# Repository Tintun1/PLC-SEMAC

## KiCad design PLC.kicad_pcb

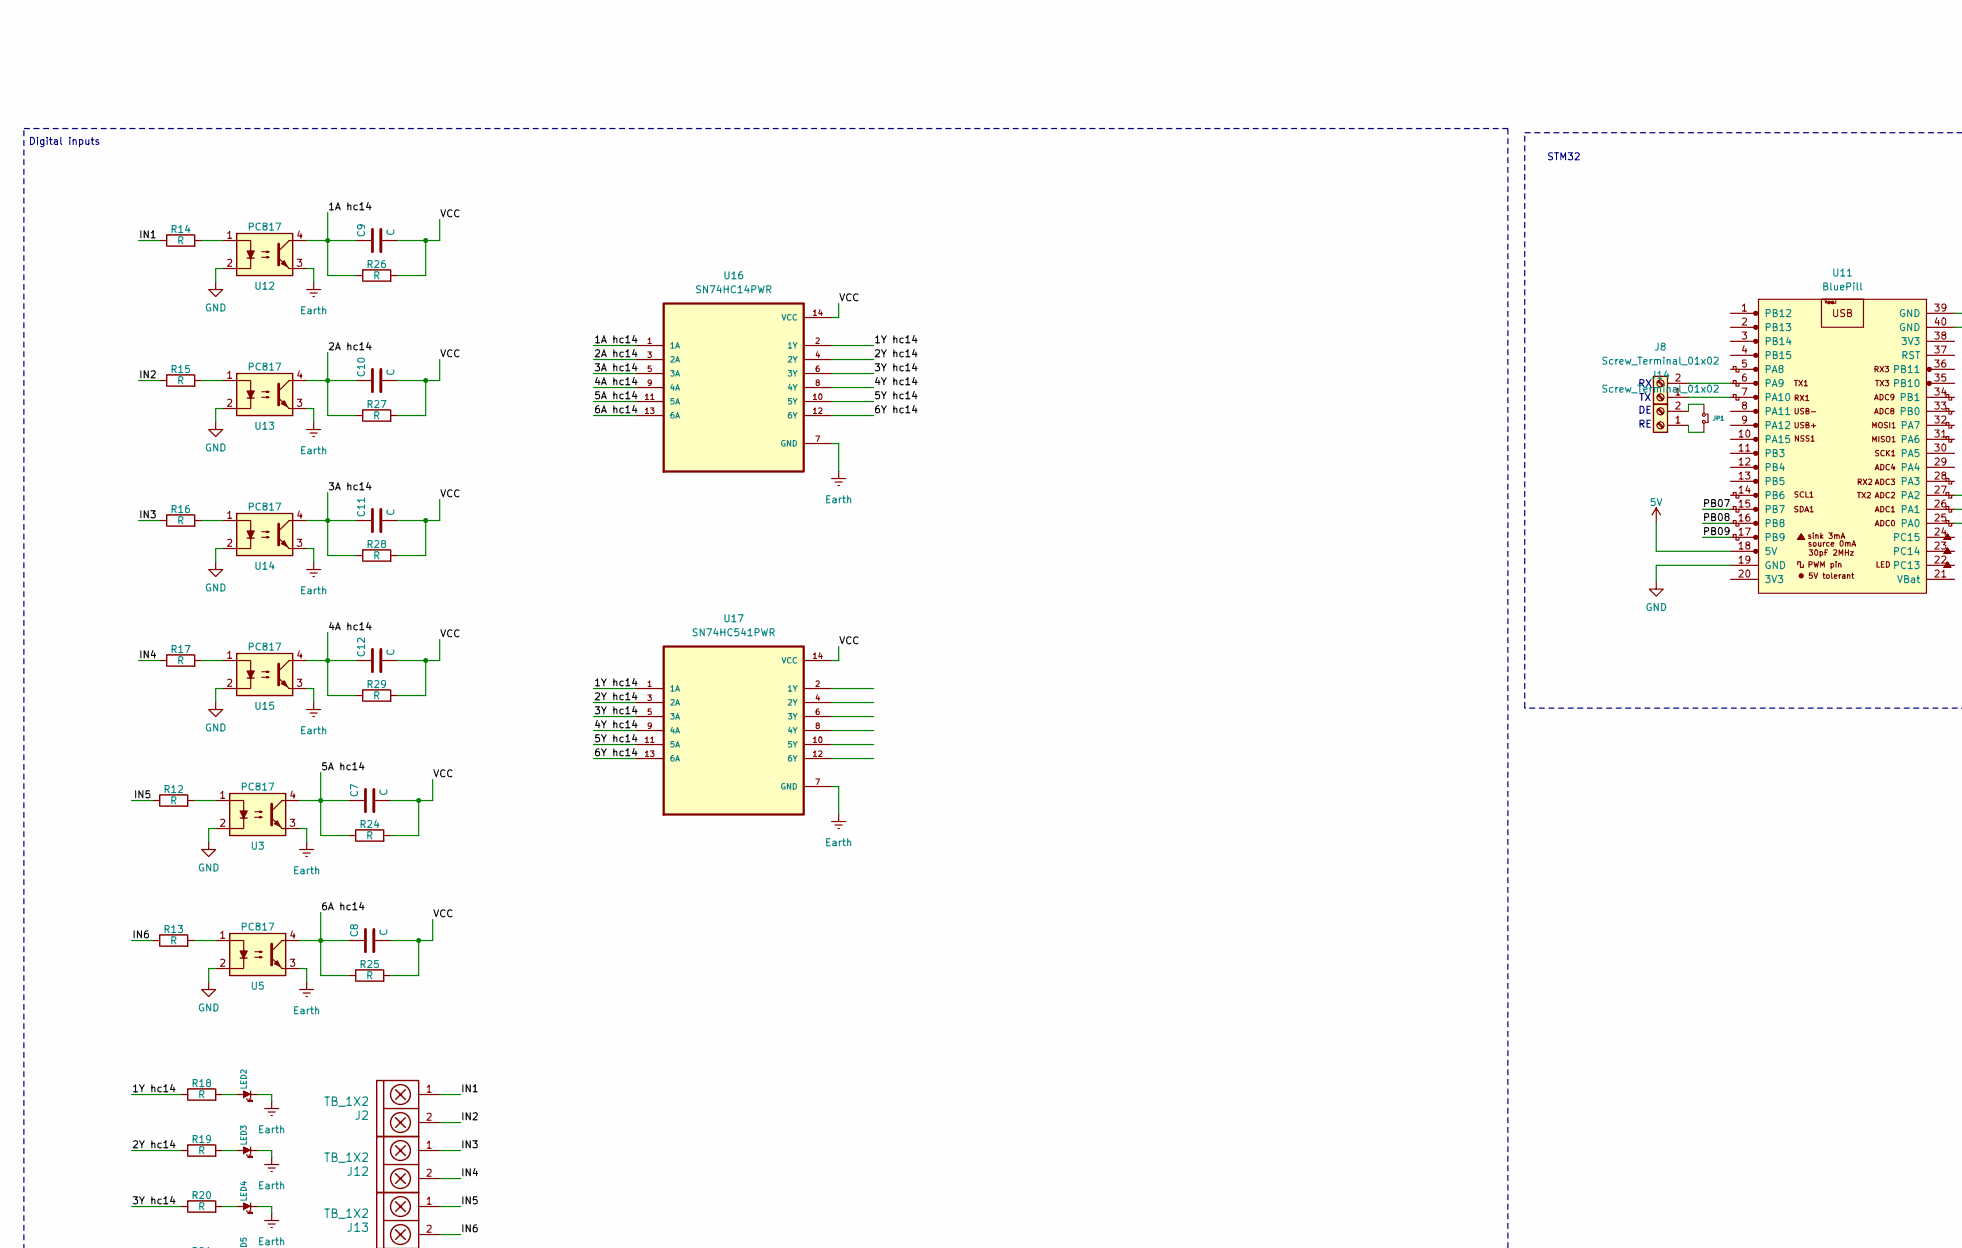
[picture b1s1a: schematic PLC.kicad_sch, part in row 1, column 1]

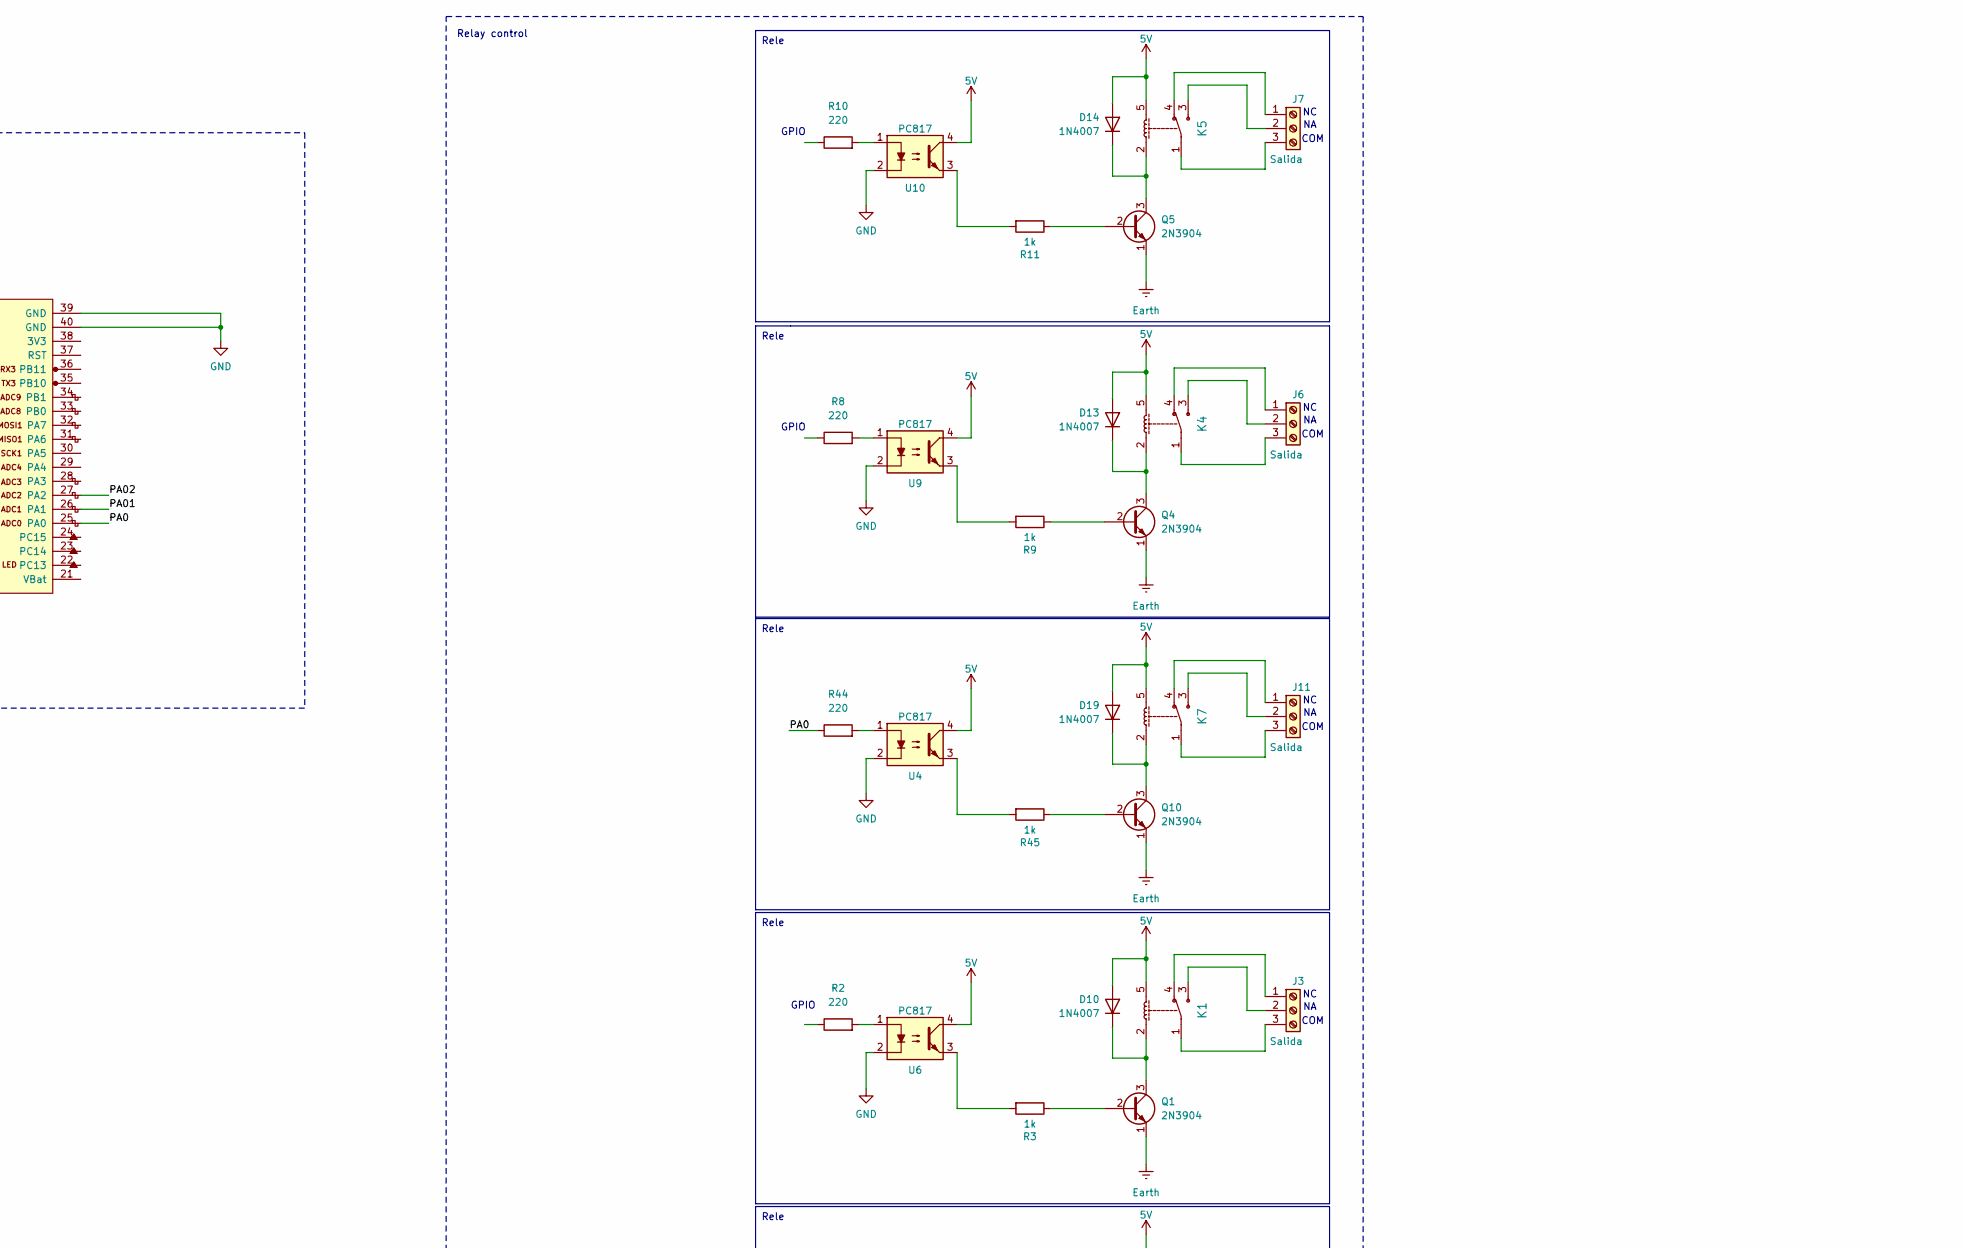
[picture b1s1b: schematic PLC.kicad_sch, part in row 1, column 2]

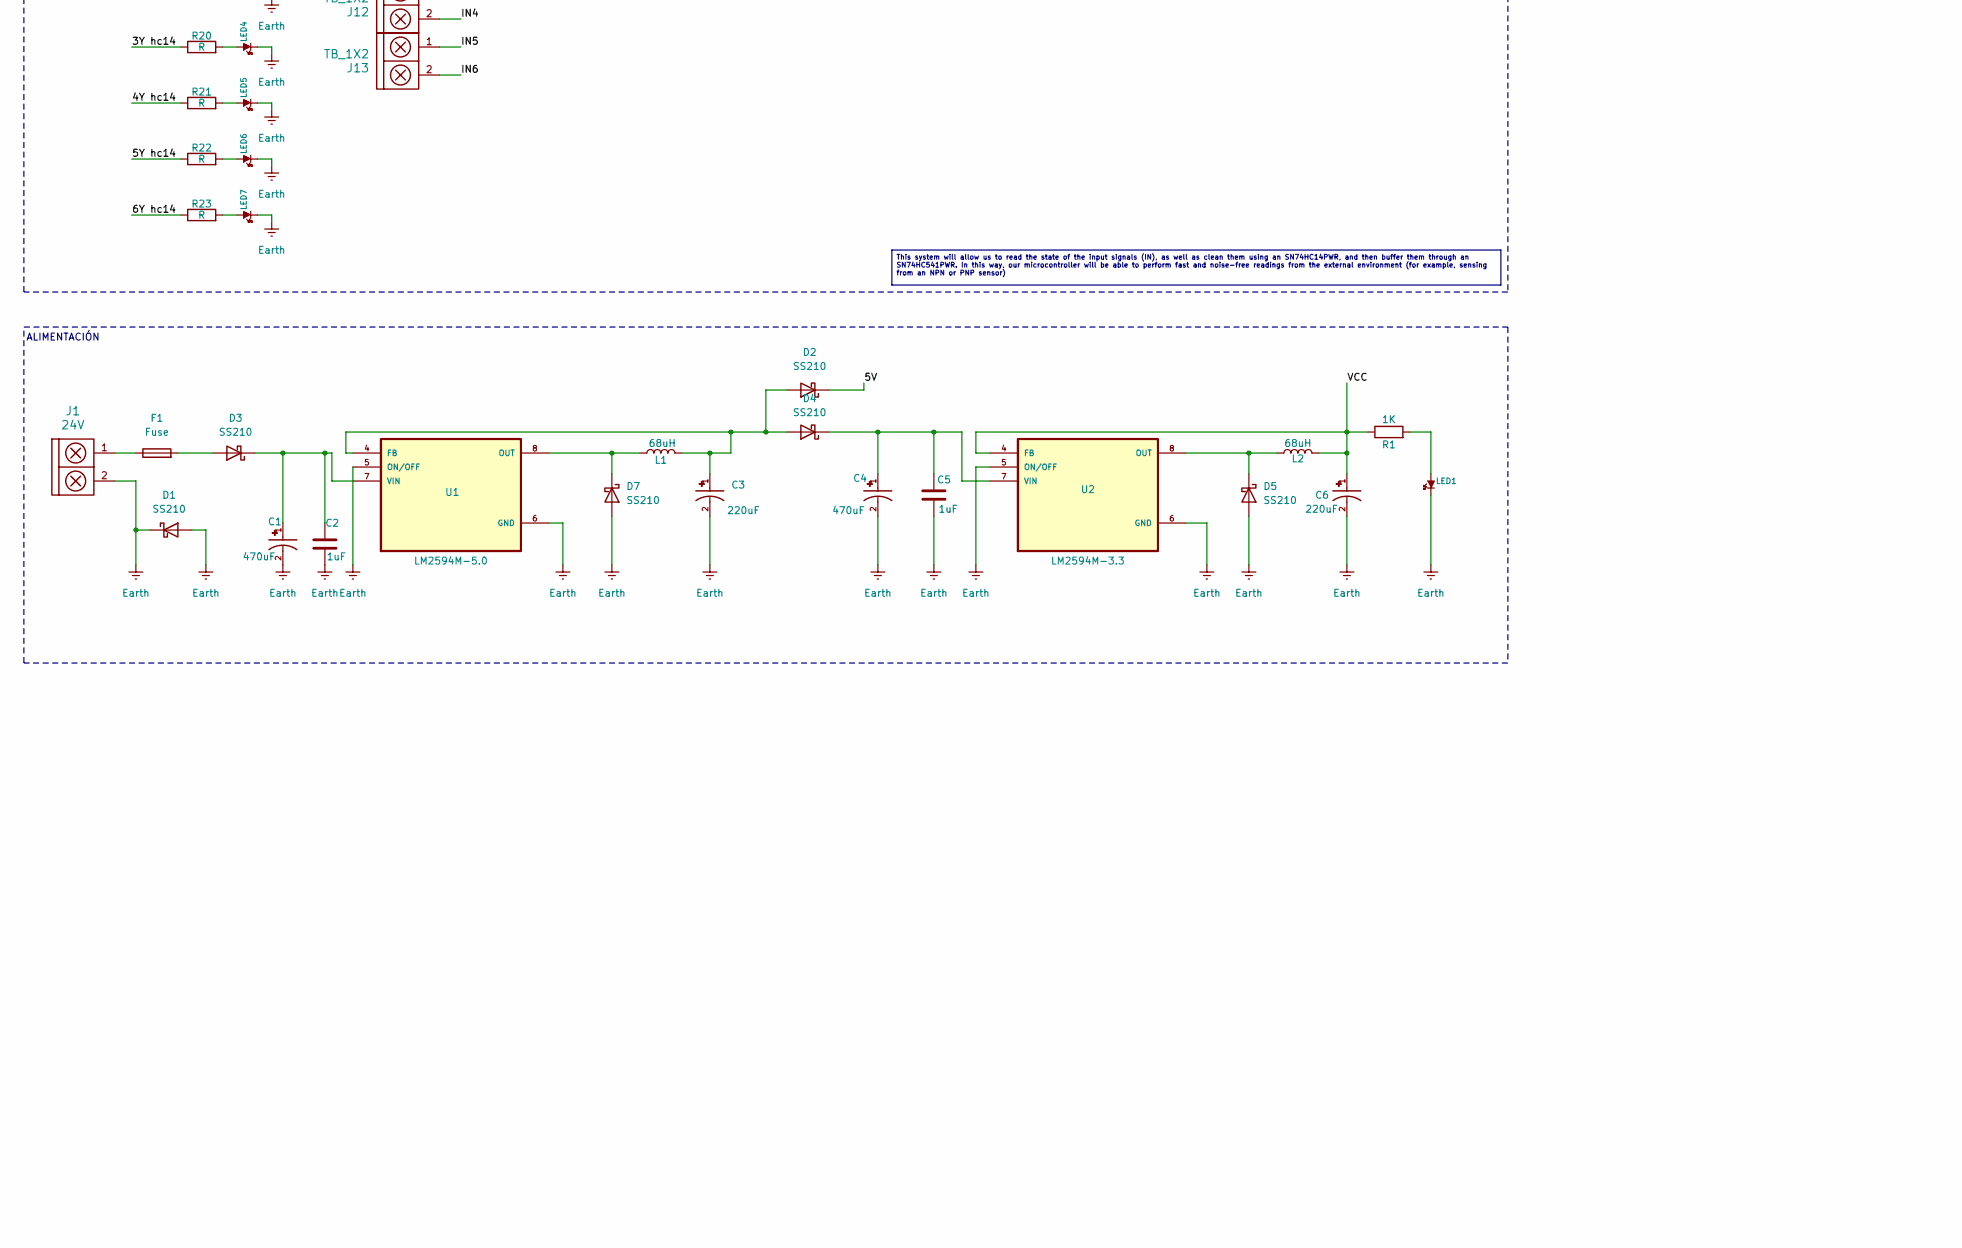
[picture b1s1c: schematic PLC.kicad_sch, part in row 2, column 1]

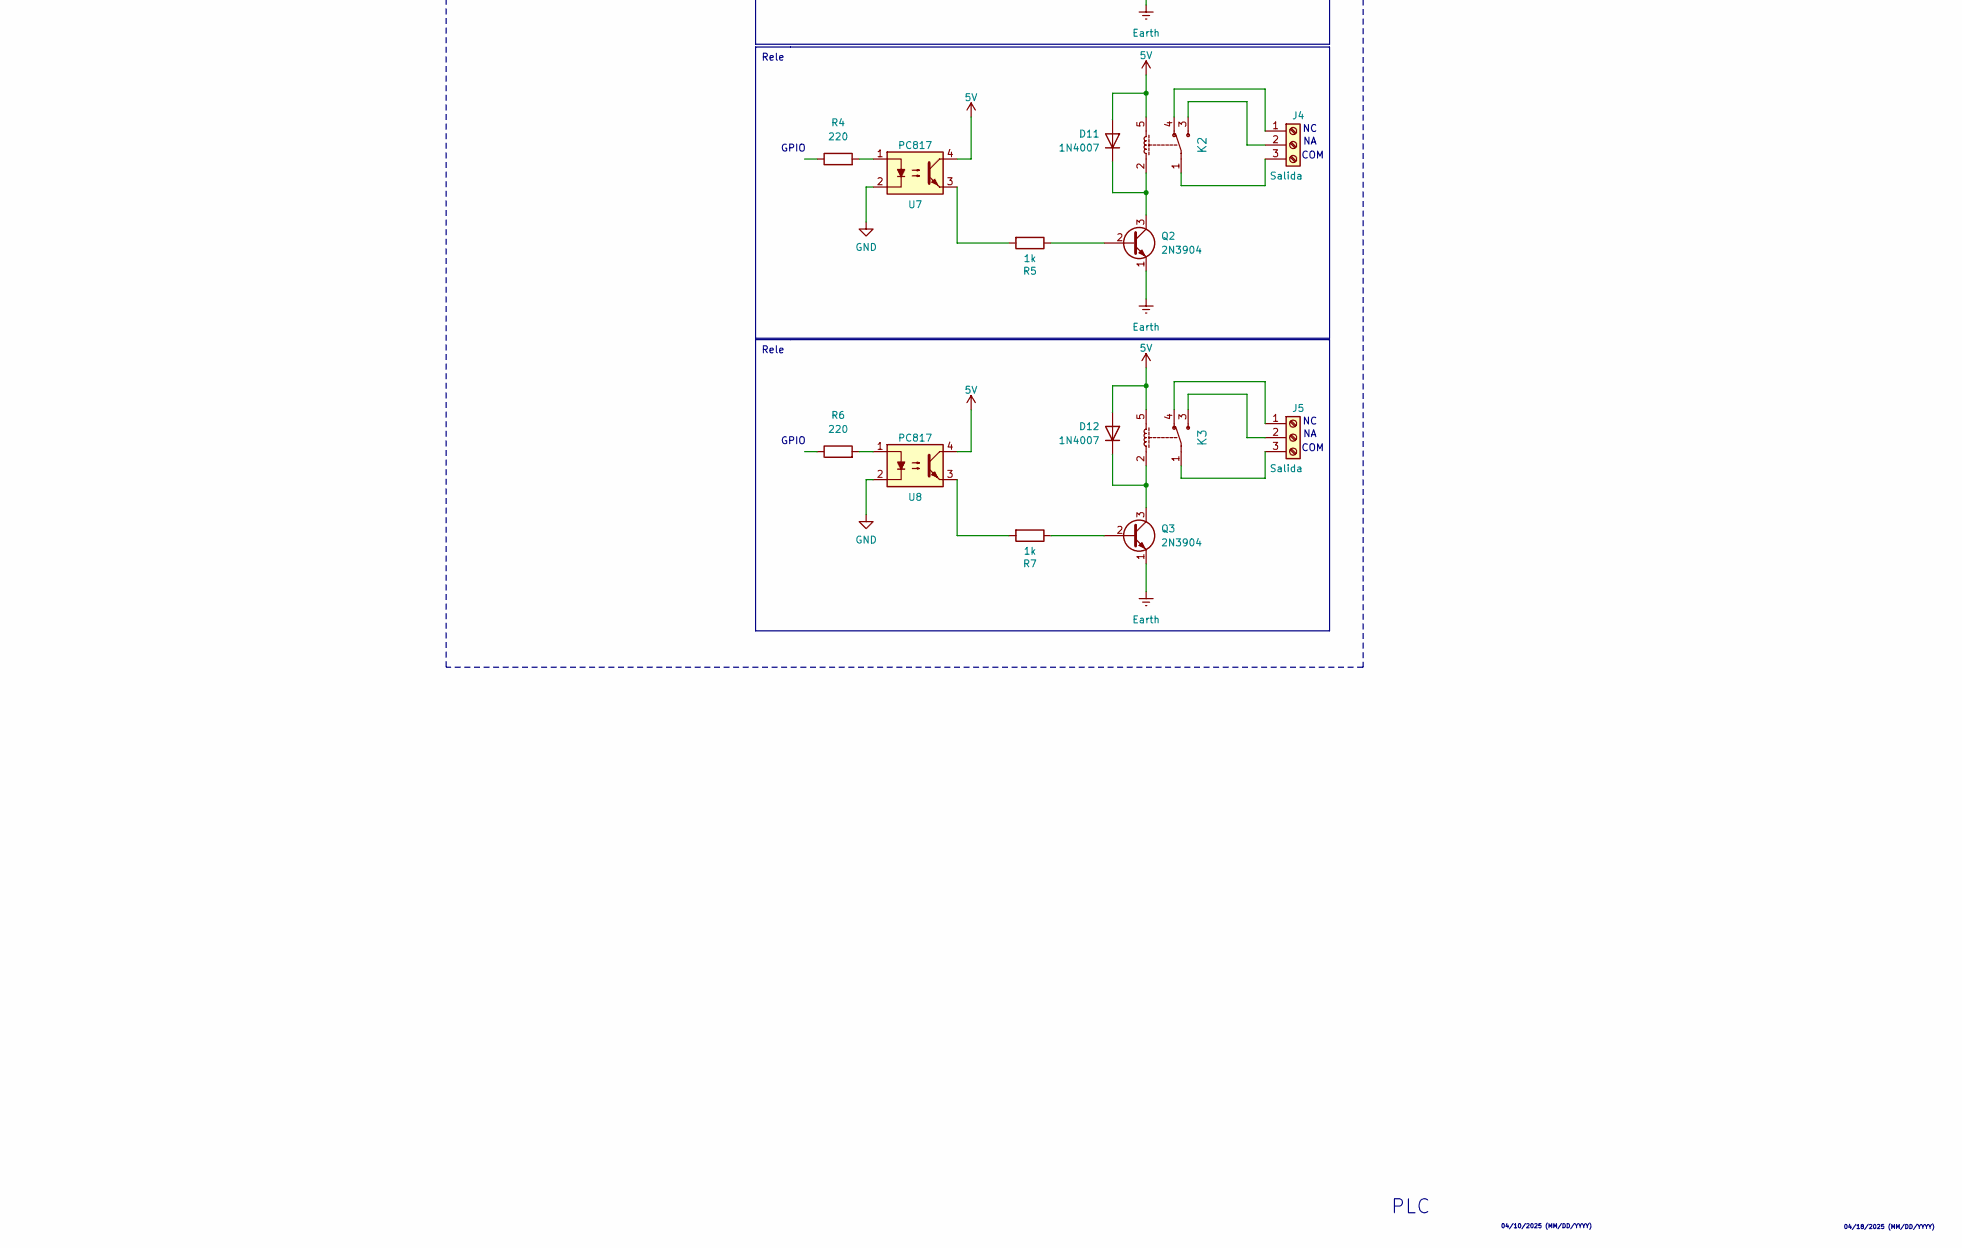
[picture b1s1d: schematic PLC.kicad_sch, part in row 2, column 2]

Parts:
C1, C4: 470uF; CP_Elec_6.3x7.7; PARTREV 10-Oct-19
C2, C5: 1uF; C_0805_2012Metric_Pad1.18x1.45mm_HandSolder
C3, C6: 220uF; CP_Elec_6.3x7.7; PARTREV 10-Oct-19
C7, C8, C9, C10, C11, C12: C; C_0805_2012Metric_Pad1.18x1.45mm_HandSolder
D1, D2, D3, D4, D5, D7: SS210; D_SMA
D10, D11, D12, D13, D14, D19: 1N4007; D_DO-41_SOD81_P10.16mm_Horizontal
F1: Fuse; FUSIBLE
J1: 24V; BORNERA2
J2, J12, J13: TB_1X2; BORNERA2
J3, J4, J5, J6, J7, J11: Salida; BORNERA3_AZUL
J8, J14: Screw_Terminal_01x02; BORNERA2
JP1: Jumper; Jumper_Alto
K1, K2, K3, K4, K5, K7: RELAY_C; Relay_C
L1, L2: 68uH; L_Bourns_SRR1260
LED1: LED; LED_0805_2012Metric
LED2, LED3, LED4, LED5, LED6, LED7: LED; led_5mm_green
Q1, Q2, Q3, Q4, Q5, Q10: 2N3904; SOT-23_Handsoldering
R1: 1K; R_0805
R2, R4, R6, R8, R10, R44: 220; R_1210_3225Metric_Pad1.30x2.65mm_HandSolder
R3, R5, R7, R9, R11, R45: 1k; R_1210_3225Metric_Pad1.30x2.65mm_HandSolder
R12, R13, R14, R15, R16, R17, R18, R19, R20, R21, R22, R23, R24, R25, R26, R27, R28, R29: R; R_0805
U1: LM2594M-5.0; SOIC-8_Hand_Soldering
U2: LM2594M-3.3; SOIC-8_Hand_Soldering
U3, U4, U5, U6, U7, U8, U9, U10, U12, U13, U14, U15: PC817; DIP-4_W7.62mm
U11: BluePill
U16: SN74HC14PWR; SOP65P640X120-14N
U17: SN74HC541PWR; SOP65P640X120-20N

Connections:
5V: D2.1 (K), D10.2 (A), D11.2 (A), D12.2 (A), D13.2 (A), D14.2 (A), D19.2 (A), K1.5, K2.5, K3.5, K4.5, K5.5, K7.5, U4.4, U6.4, U7.4, U8.4, U9.4, U10.4, U11.18 (5V)
/1A hc14: C9.1, R26.1, U12.4, U16.1 (1A)
/1Y hc14: R18.1, U16.2 (1Y), U17.1 (1A)
/2A hc14: C10.1, R27.1, U13.4, U16.3 (2A)
/2Y hc14: R19.1, U16.4 (2Y), U17.3 (2A)
/3A hc14: C11.1, R28.1, U14.4, U16.5 (3A)
/3Y hc14: R20.1, U16.6 (3Y), U17.5 (3A)
/4A hc14: C12.1, R29.1, U15.4, U16.9 (4A)
/4Y hc14: R21.1, U16.8 (4Y), U17.9 (4A)
/5A hc14: C7.1, R24.1, U3.4, U16.11 (5A)
/5Y hc14: R22.1, U16.10 (5Y), U17.11 (5A)
/6A hc14: C8.1, R25.1, U5.4, U16.13 (6A)
/6Y hc14: R23.1, U16.12 (6Y), U17.13 (6A)
/IN1: J2.1, R14.1
/IN2: J2.2, R15.1
/IN3: J12.1, R16.1
/IN4: J12.2, R17.1
/IN5: J13.1, R12.1
/IN6: J13.2, R13.1
/PA0: R44.1, U11.25 (PA0)
/PA01: U11.26 (PA1)
/PA02: U11.27 (PA2)
/PB07: U11.15 (PB7)
/PB08: U11.16 (PB8)
/PB09: U11.17 (PB9)
/VCC: C6.1, C7.2, C8.2, C9.2, C10.2, C11.2, C12.2, L2.2, R1.1, R24.2, R25.2, R26.2, R27.2, R28.2, R29.2, U2.4 (FB), U16.14 (VCC), U17.14 (VCC)
Earth: C1.2, C2.2, C3.2, C4.2, C5.2, C6.2, D1.1 (K), D1.2 (A), D5.2 (A), D7.2 (A), J1.2, LED1.2 (K), LED2.2 (K), LED3.2 (K), LED4.2 (K), LED5.2 (K), LED6.2 (K), LED7.2 (K), Q1.1 (E), Q2.1 (E), Q3.1 (E), Q4.1 (E), Q5.1 (E), Q10.1 (E), U1.5 (ON/OFF), U1.6 (GND), U2.5 (ON/OFF), U2.6 (GND), U3.3, U5.3, U12.3, U13.3, U14.3, U15.3, U16.7 (GND), U17.7 (GND)
GND: U3.2, U4.2, U5.2, U6.2, U7.2, U8.2, U9.2, U10.2, U11.19 (GND), U11.39 (GND), U11.40 (GND), U12.2, U13.2, U14.2, U15.2
unnamed: C3.1, D2.2 (A), D4.2 (A), L1.2, U1.4 (FB)
unnamed: D3.2 (A), F1.2
unnamed: C1.1, C2.1, D3.1 (K), U1.7 (VIN)
unnamed: C4.1, C5.1, D4.1 (K), U2.7 (VIN)
unnamed: D5.1 (K), L2.1, U2.8 (OUT)
unnamed: D7.1 (K), L1.1, U1.8 (OUT)
unnamed: D10.1 (K), K1.2, Q1.3 (C)
unnamed: D11.1 (K), K2.2, Q2.3 (C)
unnamed: D12.1 (K), K3.2, Q3.3 (C)
unnamed: D13.1 (K), K4.2, Q4.3 (C)
unnamed: D14.1 (K), K5.2, Q5.3 (C)
unnamed: D19.1 (K), K7.2, Q10.3 (C)
unnamed: F1.1, J1.1
unnamed: J3.1, K1.4
unnamed: J3.2, K1.3
unnamed: J3.3, K1.1
unnamed: J4.1, K2.4
unnamed: J4.2, K2.3
unnamed: J4.3, K2.1
unnamed: J5.1, K3.4
unnamed: J5.2, K3.3
unnamed: J5.3, K3.1
unnamed: J6.1, K4.4
unnamed: J6.2, K4.3
unnamed: J6.3, K4.1
unnamed: J7.1, K5.4
unnamed: J7.2, K5.3
unnamed: J7.3, K5.1
unnamed: J8.1, U11.7 (PA10)
unnamed: J8.2, U11.6 (PA9)
unnamed: J11.1, K7.4
unnamed: J11.2, K7.3
unnamed: J11.3, K7.1
unnamed: J14.1, JP1.1 (A)
unnamed: J14.2, JP1.2 (B)
unnamed: LED1.1 (A), R1.2
unnamed: LED2.1 (A), R18.2
unnamed: LED3.1 (A), R19.2
unnamed: LED4.1 (A), R20.2
unnamed: LED5.1 (A), R21.2
unnamed: LED6.1 (A), R22.2
unnamed: LED7.1 (A), R23.2
unnamed: Q1.2 (B), R3.1
unnamed: Q2.2 (B), R5.1
unnamed: Q3.2 (B), R7.1
unnamed: Q4.2 (B), R9.1
unnamed: Q5.2 (B), R11.1
unnamed: Q10.2 (B), R45.1
unnamed: R2.2, U6.1
unnamed: R3.2, U6.3
unnamed: R4.2, U7.1
unnamed: R5.2, U7.3
unnamed: R6.2, U8.1
unnamed: R7.2, U8.3
unnamed: R8.2, U9.1
unnamed: R9.2, U9.3
unnamed: R10.2, U10.1
unnamed: R11.2, U10.3
unnamed: R12.2, U3.1
unnamed: R13.2, U5.1
unnamed: R14.2, U12.1
unnamed: R15.2, U13.1
unnamed: R16.2, U14.1
unnamed: R17.2, U15.1
unnamed: R44.2, U4.1
unnamed: R45.2, U4.3

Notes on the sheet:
This system will allow us to read the state of the input signals (IN), as well as clean them using an SN74HC14PWR, and then buffer them through an SN74HC541PWR. In this way, our microcontroller will be able to perform fast and noise-free readings from the external environment (for example, sensing 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
04/10/2025 (MM/DD/YYYY)
STM32
04/18/2025 (MM/DD/YYYY)
Rele
GPIO
Relay control
PLC
COM
Digital inputs
ALIMENTACIÓN

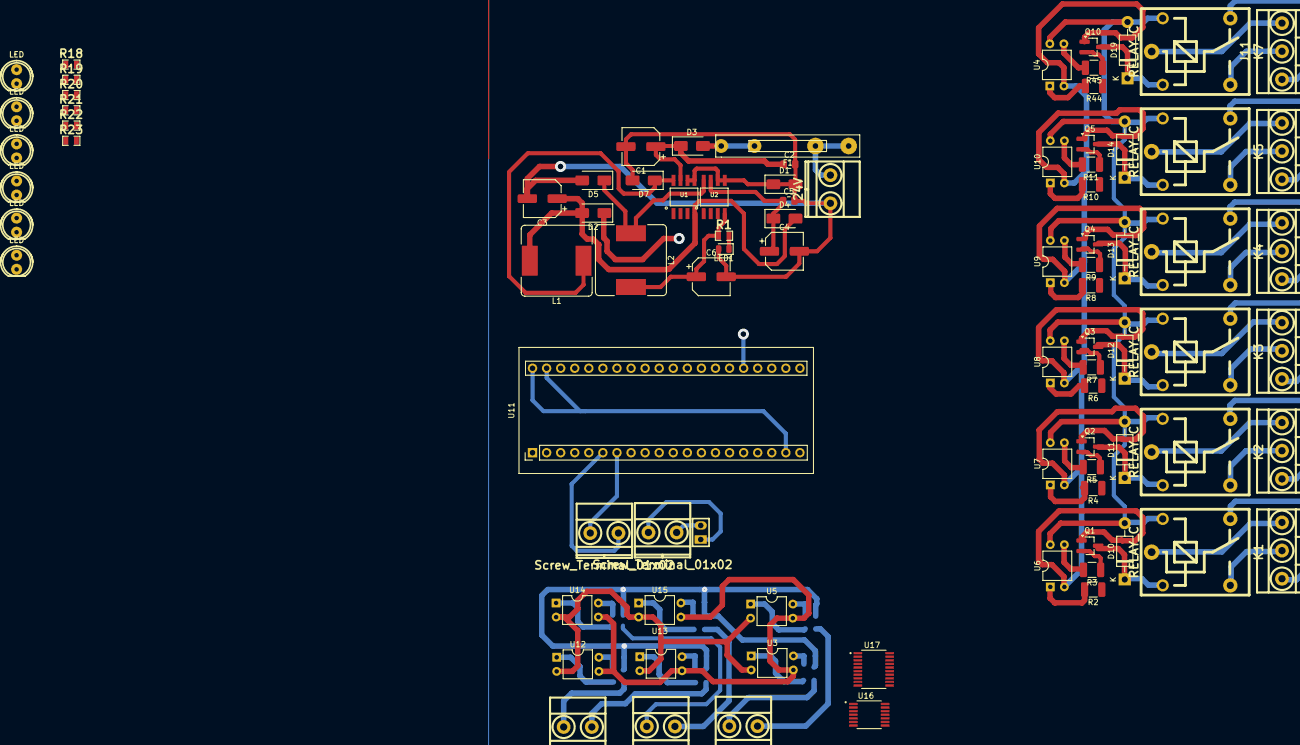
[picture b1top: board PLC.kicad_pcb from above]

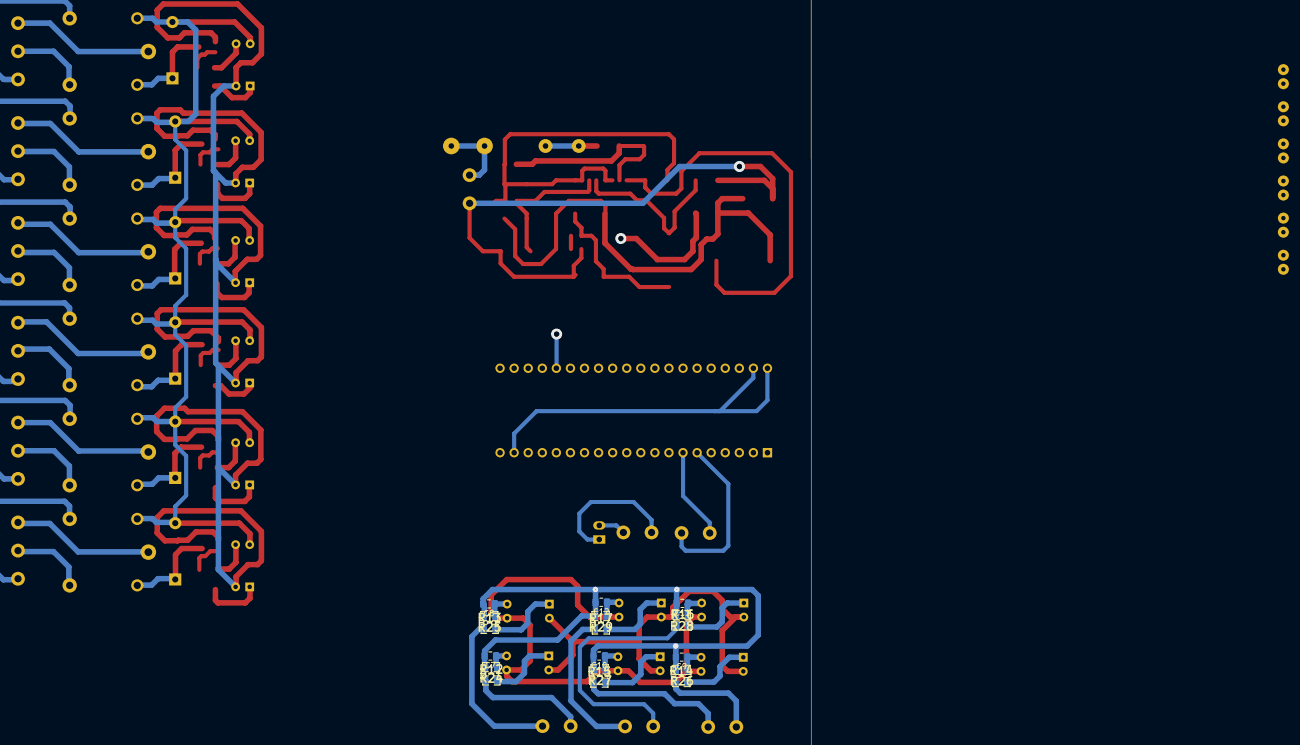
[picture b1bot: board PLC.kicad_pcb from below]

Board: 2 copper layers, 107 parts (18 on the bottom side), 89 nets.

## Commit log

2025-04-12 esquemático y pcb
    esquema y pcb
2025-04-12 revisión 0.1
2025-04-16 Librerias locales
    modif Modulos rele
    Librerias locales
    -
    Tenes que pasar las huellas y simbolos a librerias locales, asi el proyecto es portable
2025-04-18 PLC (revisón 0.2)
2025-04-29 Revisión 0.3 (PCB)
    primera fase de la PCB
2025-05-01 Revisión 0.4 (PCB)
2025-05-01 act pcb
    hace que ocupe menos espacio
    ahi te corregi unas cosas
2025-05-03 Revisión 0.5 (PCB)
2025-05-04 Arreglo
    .
2025-05-04 act1
    ..
2025-05-05 Revisión 0.6 (PCB)
2025-05-05 act2
    acommod
2025-05-07 Revision 0.6 (fin proto PCB)
2025-05-23 Revision 0.7 (BUCKS)
